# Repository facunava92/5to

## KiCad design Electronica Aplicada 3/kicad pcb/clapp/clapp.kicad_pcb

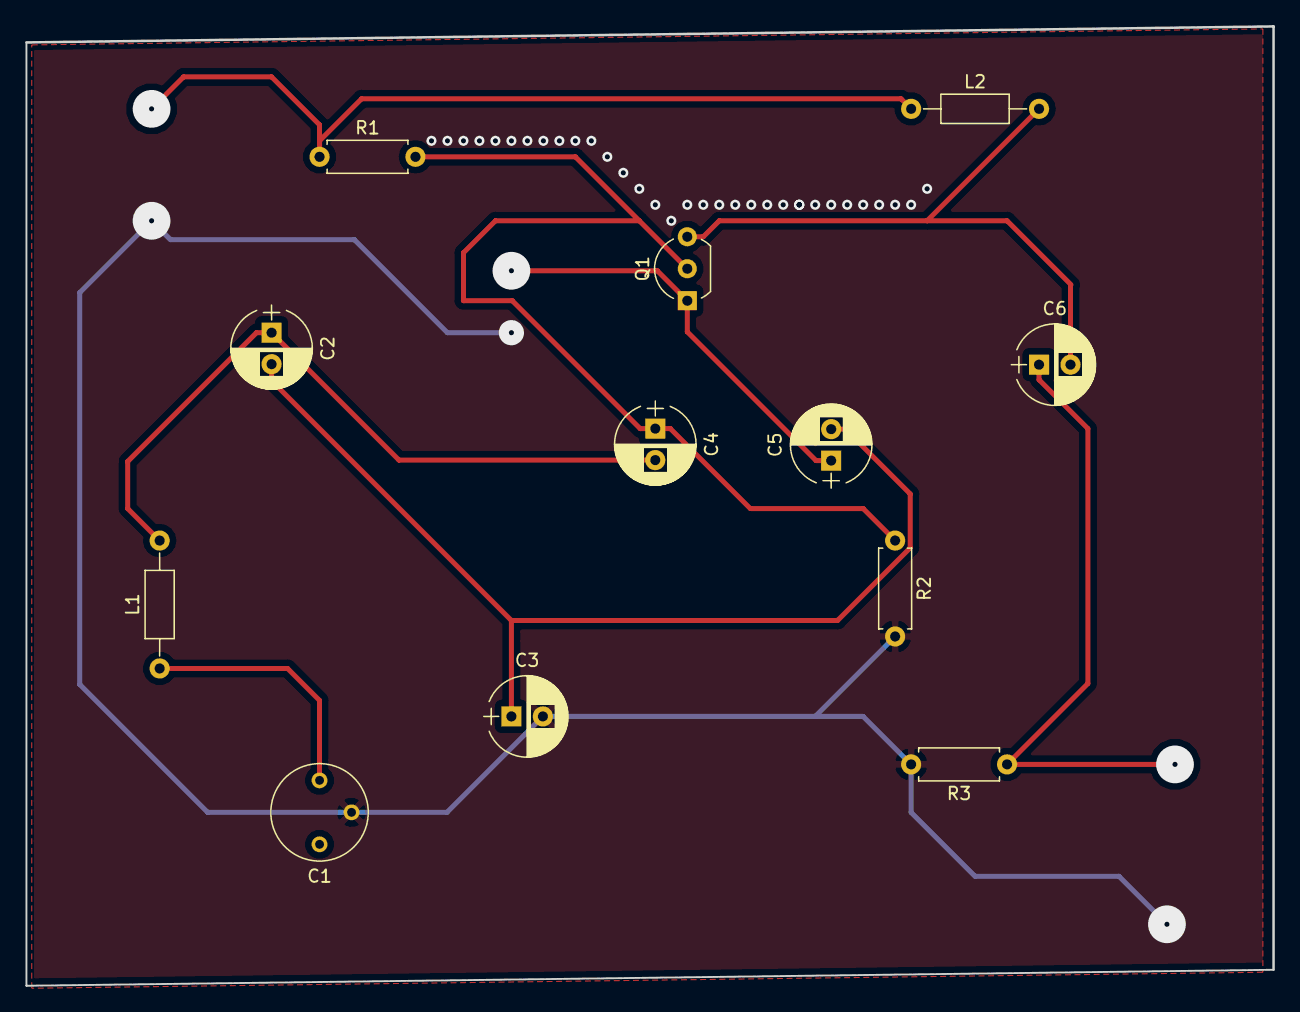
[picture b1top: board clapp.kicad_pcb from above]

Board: 2 copper layers, 99.1 x 76.2 mm, 12 parts (0 on the bottom side), 9 nets.

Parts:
C1: C_Variable; Potentiometer_Trimmer_Bourns_3339P_Horizontal
C2, C3, C4, C5, C6: C; CP_Radial_D6.3mm_P2.50mm
L1, L2: L; L_Axial_L5.3mm_D2.2mm_P10.16mm_Horizontal_Vishay_IM-1
Q1: 2N3904; TO-92_Inline_Wide
R1, R2, R3: R; R_Axial_DIN0207_L6.3mm_D2.5mm_P7.62mm_Horizontal

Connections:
GND: C1.2, C3.2, R2.2, R3.2
unnamed: C1.1, L1.1
unnamed: C2.1, C4.2, L1.2
unnamed: C2.2, C3.1, C5.2
unnamed: C4.1, Q1.2, R1.2, R2.1
unnamed: C5.1, Q1.1
unnamed: C6.1, R3.1
unnamed: C6.2, L2.2, Q1.3
unnamed: L2.1, R1.1

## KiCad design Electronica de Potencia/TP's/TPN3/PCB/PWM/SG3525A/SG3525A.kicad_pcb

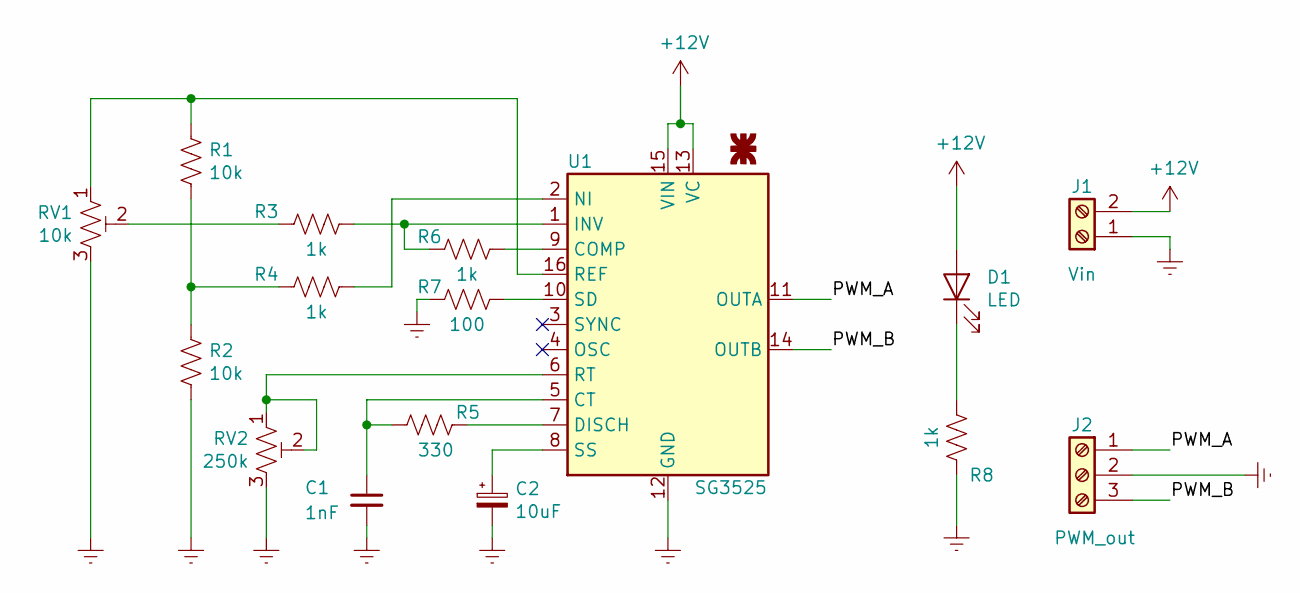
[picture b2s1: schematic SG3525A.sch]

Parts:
C1: 1nF; C_Disc_D4.7mm_W2.5mm_P5.00mm
C2: 10uF; C_Radial_D5.0mm_H11.0mm_P2.00mm
D1: LED; LED_D3.0mm_Clear
G1: logo; logo_utn_fsilk_small
J1: Vin; TerminalBlock_bornier-2_P5.08mm
J2: PWM_out; TerminalBlock_bornier-3_P5.08mm
R1, R2: 10k; R_Axial_DIN0207_L6.3mm_D2.5mm_P10.16mm_Horizontal
R3, R4, R6, R8: 1k; R_Axial_DIN0207_L6.3mm_D2.5mm_P10.16mm_Horizontal
R5: 330; R_Axial_DIN0207_L6.3mm_D2.5mm_P10.16mm_Horizontal
R7: 100; R_Axial_DIN0207_L6.3mm_D2.5mm_P10.16mm_Horizontal
RV1: 10k; Potentiometer_Bourns_3266Y_Vertical
RV2: 250k; Potentiometer_Bourns_3266Y_Vertical
U1: SG3525; DIP-16_W7.62mm_LongPads

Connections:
+12V: D1.2 (A), J1.2, U1.13 (VC), U1.15 (VIN)
/PWM_A: J2.1, U1.11 (OUTA)
/PWM_B: J2.3, U1.14 (OUTB)
Earth: C1.2, C2.2, J1.1, J2.2, R2.1, R7.1, R8.2, RV1.3, RV2.3, U1.12 (GND)
unnamed: C1.1, R5.1, U1.5 (CT)
unnamed: C2.1, U1.8 (SS)
unnamed: D1.1 (K), R8.1
unnamed: R1.1, R2.2, R4.1
unnamed: R1.2, RV1.1, U1.16 (REF)
unnamed: R3.1, RV1.2
unnamed: R3.2, R6.1, U1.1 (INV)
unnamed: R4.2, U1.2 (NI)
unnamed: R5.2, U1.7 (DISCH)
unnamed: R6.2, U1.9 (COMP)
unnamed: R7.2, U1.10 (SD)
unnamed: RV2.1, RV2.2, U1.6 (RT)

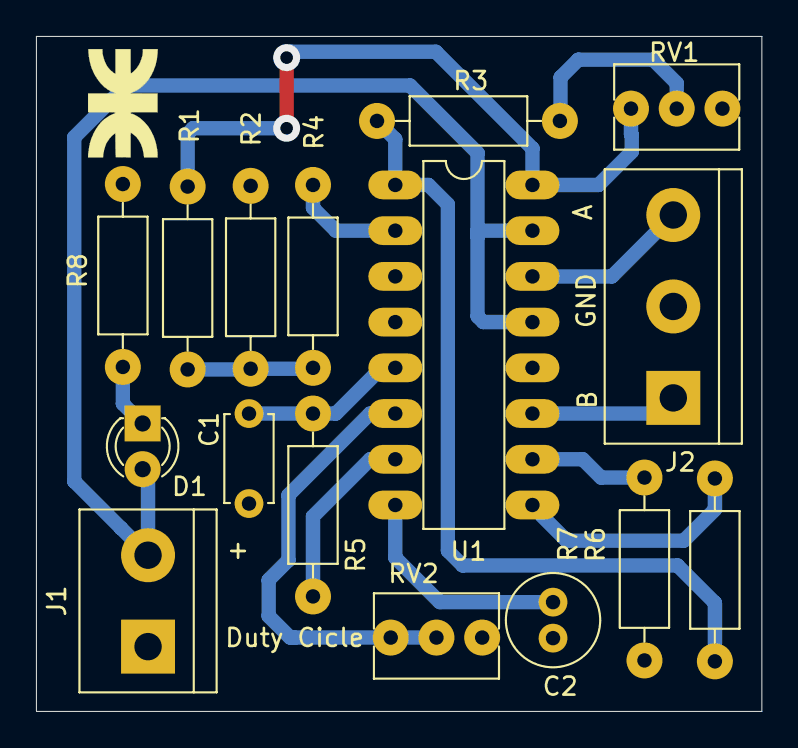
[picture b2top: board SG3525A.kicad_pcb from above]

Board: 2 copper layers, 40.3 x 37.5 mm, 17 parts (0 on the bottom side), 16 nets.
